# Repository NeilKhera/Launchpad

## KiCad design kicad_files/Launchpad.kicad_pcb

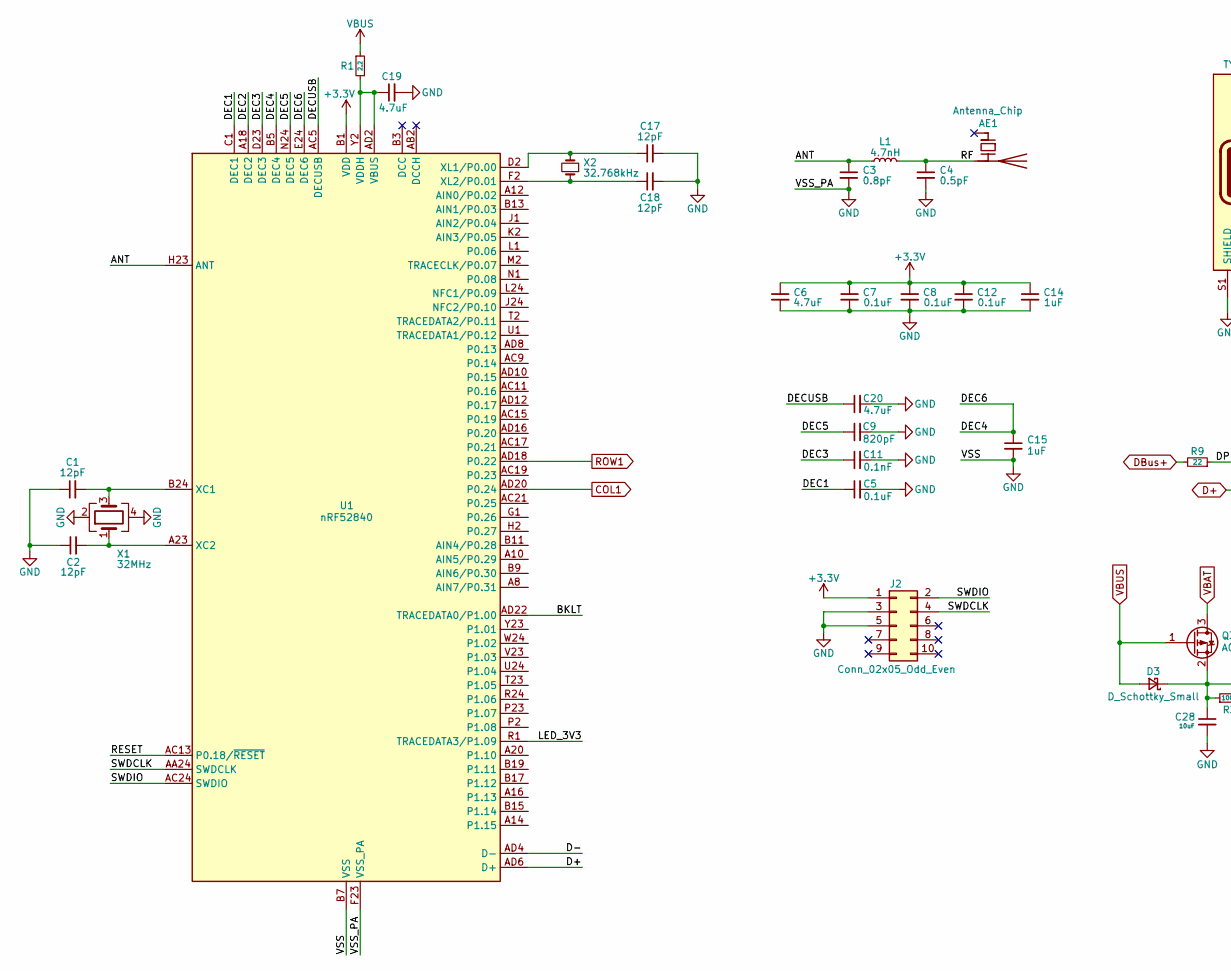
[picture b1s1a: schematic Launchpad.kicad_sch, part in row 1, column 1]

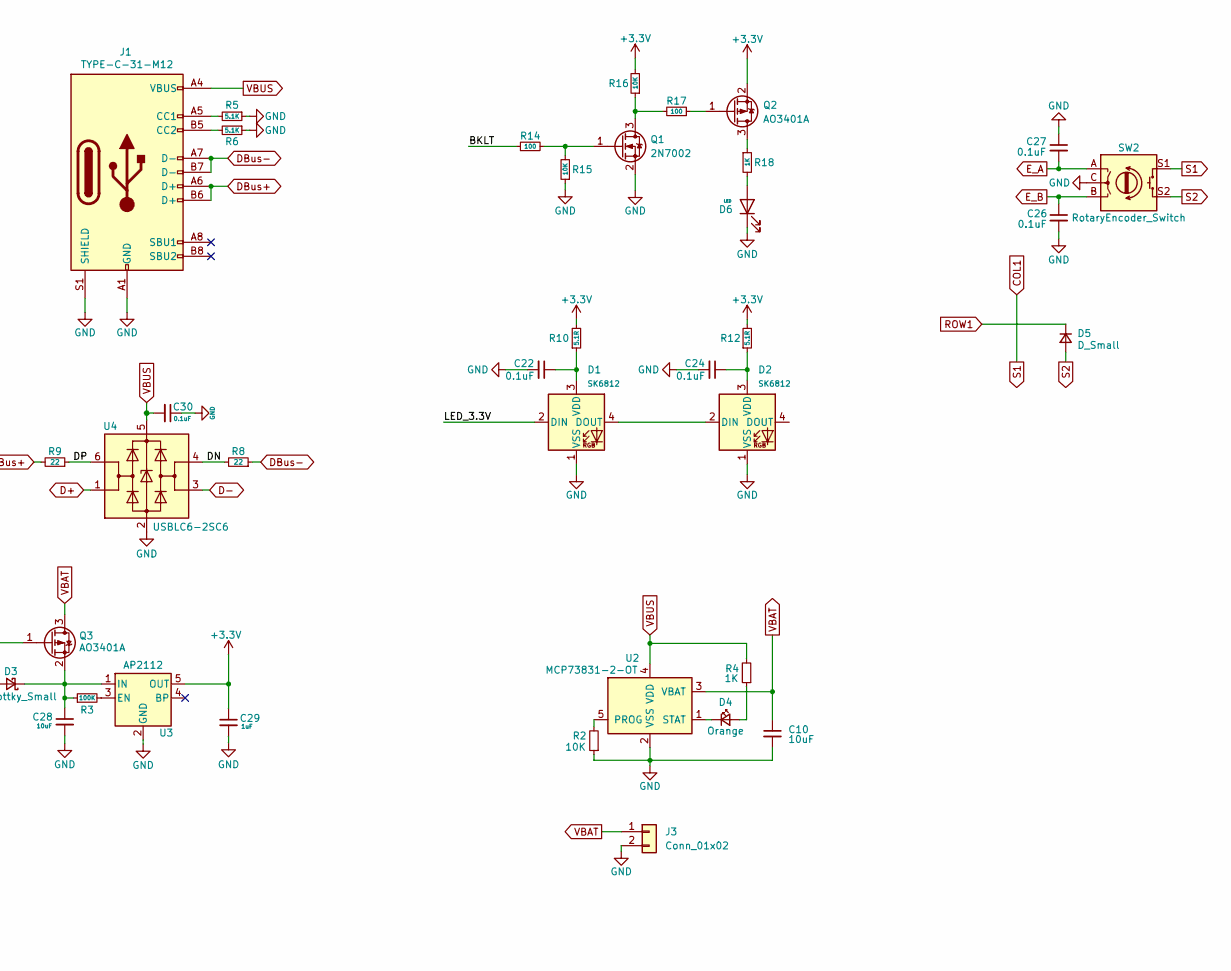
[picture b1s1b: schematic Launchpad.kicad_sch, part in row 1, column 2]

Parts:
AE1: Antenna_Chip; 2450AT42A100E
C1, C2, C17, C18: 12pF; C_0603_1608Metric
C3: 0.8pF; C_0402_1005Metric
C4: 0.5pF; C_0402_1005Metric
C5, C7, C8, C12, C30: 0.1uF; C_0603_1608Metric
C6, C19, C20: 4.7uF; C_0603_1608Metric
C9: 820pF; C_0603_1608Metric
C10, C28: 10uF; C_0603_1608Metric
C11: 0.1nF; C_0603_1608Metric
C14, C15, C29: 1uF; C_0603_1608Metric
C22, C24, C26, C27: 0.1uF; C_0603_1608Metric; Manufacturer Part Number CL05B104KB54PNC
D1, D2: SK6812; LED_SK6812_PLCC4_5.0x5.0mm_P3.2mm
D3: D_Schottky_Small; D_SOD-123F
D4: Orange; LED_0805_2012Metric_Pad1.15x1.40mm_HandSolder
D5: D_Small; D_SOD-123
D6: LED; LED_0805_2012Metric_Pad1.15x1.40mm_HandSolder
J1: TYPE-C-31-M12; USB_C_Receptacle_Hroparts_TYPE-C-31-M-12
J2: Conn_02x05_Odd_Even; PinHeader_2x05_P1.27mm_Vertical_SMD
J3: Conn_01x02; JSTPH2
L1: 4.7nH; L_0402_1005Metric
Q1: 2N7002; SOT-23; Manufacturer Part Number 2N7002
Q2: AO3401A; SOT-23; Manufacturer Part Number Alpha & Omega Semicon
Q3: AO3401A; SOT-23
R1: 2.2; R_0603_1608Metric
R2: 10K; R_0603_1608Metric
R3: 100K; R_0603_1608Metric
R4: 1K; R_0603_1608Metric
R5, R6: 5.1K; R_0603_1608Metric
R8, R9: 22; R_0603_1608Metric
R10, R12: 5.1R; R_0603_1608Metric; Manufacturer Part Number 0402WGJ033JTCE
R14, R17: 100; R_0603_1608Metric; Manufacturer Part Number 0402WGF1000TCE
R15, R16: 10K; R_0603_1608Metric; Manufacturer Part Number 0402WGF1002TCE
R18: 1K; R_0805_2012Metric_Pad1.20x1.40mm_HandSolder; Manufacturer Part Number 0805W8F1001T5E
SW2: RotaryEncoder_Switch; ALPS_EC11E
U1: nRF52840; NORDIC_NRF52840-QIAA-R7
U2: MCP73831-2-OT; SOT-23-5
U3: AP2112; SOT-23-5
U4: USBLC6-2SC6; SOT-23-6
X1: 32MHz; Crystal_SMD_2520-4Pin_2.5x2.0mm
X2: 32.768kHz; Crystal_SMD_2012-2Pin_2.0x1.2mm_HandSoldering

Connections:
+3V3: C6.1, C7.1, C8.1, C12.1, C14.1, C29.1, J2.1, Q2.2 (S), R10.2, R12.2, R16.2, U1.A22 (VDD), U1.AD14 (VDD), U1.AD23 (VDD), U1.B1 (VDD), U1.W1 (VDD), U3.5 (OUT)
/ANT: C3.1, L1.1, U1.H23 (ANT)
/BKLT: R14.1, U1.AD22 (TRACEDATA0/P1.00)
/DEC1: C5.1, U1.C1 (DEC1)
/DEC2: U1.A18 (DEC2)
/DEC3: C11.1, U1.D23 (DEC3)
/DEC4: C15.1, U1.B5 (DEC4), U1.E24 (DEC6)
/DEC5: C9.1, U1.N24 (DEC5)
/DECUSB: C20.1, U1.AC5 (DECUSB)
/DN: R8.2, U4.4 (I/O2)
/DP: R9.1, U4.6 (I/O1)
/LED_3.3V: D1.2 (DIN)
/LED_3V3: U1.R1 (TRACEDATA3/P1.09)
/RESET: U1.AC13 (P0.18/~RESET)
/RF: AE1.2 (PCB_Trace), C4.1, L1.2
/SWDCLK: J2.4, U1.AA24 (SWDCLK)
/SWDIO: J2.2, U1.AC24 (SWDIO)
COL1: SW2.S1, U1.AD20 (P0.24)
D+: U1.AD6 (D+), U4.1 (I/O1)
D-: U1.AD4 (D-), U4.3 (I/O2)
DBus+: J1.A6 (D+), J1.B6 (D+), R9.2
DBus-: J1.A7 (D-), J1.B7 (D-), R8.1
E_A: C27.2, SW2.A
E_B: C26.1, SW2.B
GND: C1.1, C2.1, C3.2, C4.2, C5.2, C6.2, C7.2, C8.2, C9.2, C10.2, C11.2, C12.2, C14.2, C15.2, C17.2, C18.2, C19.2, C20.2, C22.2, C24.2, C26.2, C27.1, C28.2, C29.2, C30.1, D1.1 (VSS), D2.1 (VSS), D6.1 (K), J1.A1 (GND), J1.B1 (GND), J1.S1 (SHIELD), J2.3, J2.5, J3.2, Q1.2 (S), R2.1, R5.1, R6.1, R15.1, SW2.C, U1.B7 (VSS), U1.EP (VSS), U1.F23 (VSS_PA), U2.2 (VSS), U3.2 (GND), U4.2 (GND), X1.2, X1.4
unnamed: C1.2, U1.B24 (XC1), X1.3
unnamed: C2.2, U1.A23 (XC2), X1.1
unnamed: C17.1, U1.D2 (XL1/P0.00), X2.2
unnamed: C18.1, U1.F2 (XL2/P0.01), X2.1
unnamed: C19.1, R1.2, U1.AD2 (VBUS), U1.Y2 (VDDH)
unnamed: C22.1, D1.3 (VDD), R10.1
unnamed: C24.1, D2.3 (VDD), R12.1
unnamed: C28.1, D3.1 (K), Q3.2 (S), R3.1, U3.1 (IN)
unnamed: D1.4 (DOUT), D2.2 (DIN)
unnamed: D4.1 (K), U2.1 (STAT)
unnamed: D4.2 (A), R4.1
unnamed: D6.2 (A), R18.2
unnamed: J1.A5 (CC1), R5.2
unnamed: J1.B5 (CC2), R6.2
unnamed: Q1.1 (G), R14.2, R15.2
unnamed: Q1.3 (D), R16.1, R17.2
unnamed: Q2.1 (G), R17.1
unnamed: Q2.3 (D), R18.1
unnamed: R2.2, U2.5 (PROG)
unnamed: R3.2, U3.3 (EN)
ROW1: D5.1 (K), U1.AD18 (P0.22)
S2: D5.2 (A), SW2.S2
VBAT: C10.1, J3.1, Q3.3 (D), U2.3 (VBAT)
VBUS: C30.2, D3.2 (A), J1.A4 (VBUS), J1.B4 (VBUS), Q3.1 (G), R1.1, R4.2, U2.4 (VDD), U4.5 (VBUS)

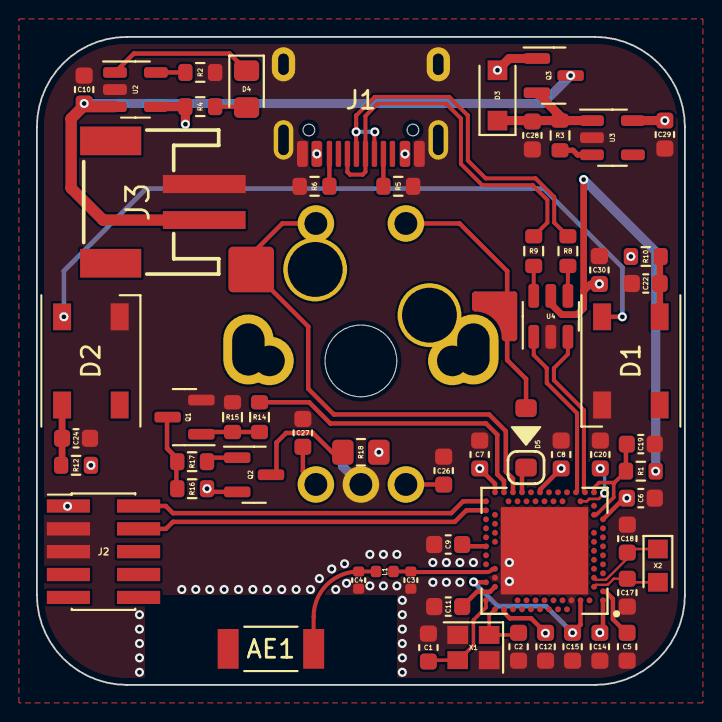
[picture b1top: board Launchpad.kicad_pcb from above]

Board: 2 copper layers, 36.0 x 36.0 mm, 61 parts (1 on the bottom side), 45 nets.

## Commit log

2022-04-20 V1 Routing Done
2022-04-20 Removed submodule changes
2022-08-21 V2 Changes
2022-09-13 Added Mini Launchpad
2022-09-19 Stuff
2022-12-23 Stash 2

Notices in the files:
parts and their libraries:
Copyright 2021 Accelerated Designs. All rights reserved.
